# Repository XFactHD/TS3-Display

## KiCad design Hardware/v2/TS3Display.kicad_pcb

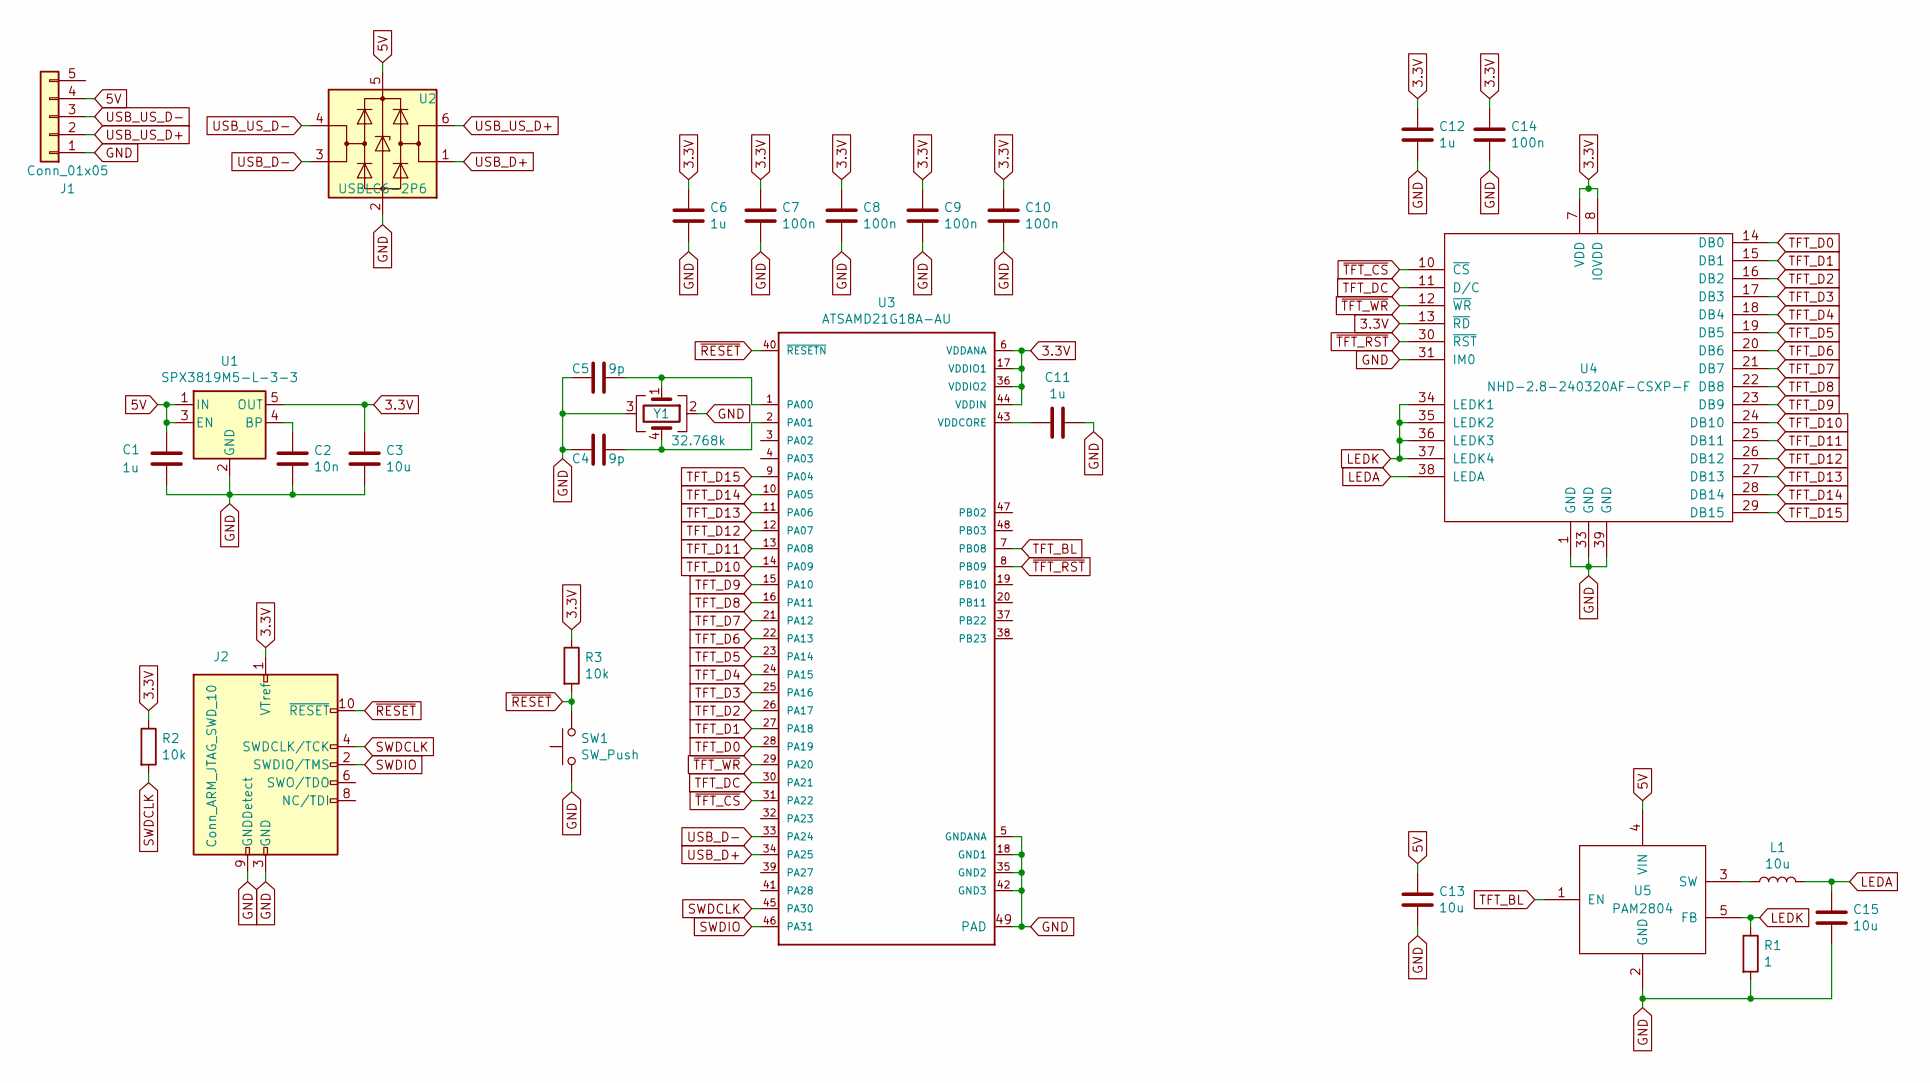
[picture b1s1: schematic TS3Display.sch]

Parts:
C1, C6, C11, C12: 1u; C_0805
C2: 10n; C_0805
C3, C13, C15: 10u; C_0805
C4, C5: 9p; C_0805
C7: 100n; C_0603
C8, C9, C10, C14: 100n; C_0805
J1: Conn_01x05; JST_SH_BM05B-SRSS-TB_05x1.00mm_Straight
J2: Conn_ARM_JTAG_SWD_10; Pin_Header_Straight_2x05_Pitch1.27mm_SMD
L1: 10u; L_Taiyo-Yuden_NR-40xx
R1: 1; R_0805
R2, R3: 10k; R_0805
SW1: SW_Push; SW_SPST_PTS810
U1: SPX3819M5-L-3-3; SOT-23-5
U2: USBLC6-2P6; SOT-23-6
U3: ATSAMD21G18A-AU; QFN-48-1EP_7x7mm_Pitch0.5mm
U4: NHD-2.8-240320AF-CSXP-F
U5: PAM2804; TSOT-23-5
Y1: 32.768k; Crystal_SMD_SeikoEpson_MC146-4pin_6.7x1.5mm

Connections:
3.3V: C3.1, C6.1, C7.1, C8.1, C9.1, C10.1, C12.1, C14.1, J2.1 (VTref), R2.1, R3.1, U1.5 (OUT), U3.6 (VDDANA), U3.17 (VDDIO1), U3.36 (VDDIO2), U3.44 (VDDIN), U4.7 (VDD), U4.8 (IOVDD), U4.13 (~RD)
5V: C1.1, C13.2, J1.4, U1.1 (IN), U1.3 (EN), U2.5 (VBUS), U5.4 (VIN)
GND: C1.2, C2.1, C3.2, C4.2, C5.2, C6.2, C7.2, C8.2, C9.2, C10.2, C11.1, C12.2, C13.1, C14.2, C15.1, J1.1, J2.3 (GND), J2.5 (GND), J2.9 (GNDDetect), R1.2, SW1.1, U1.2 (GND), U2.2 (GND), U3.5 (GNDANA), U3.18 (GND1), U3.35 (GND2), U3.42 (GND3), U3.49 (PAD), U4.1 (GND), U4.31 (IM0), U4.33 (GND), U4.39 (GND), U5.2 (GND), Y1.2, Y1.3
LEDA: C15.2, L1.2, U4.38 (LEDA)
LEDK: R1.1, U4.34 (LEDK1), U4.35 (LEDK2), U4.36 (LEDK3), U4.37 (LEDK4), U5.5 (FB)
unnamed: C2.2, U1.4 (BP)
unnamed: C4.1, U3.2 (PA01), Y1.4
unnamed: C5.1, U3.1 (PA00), Y1.1
unnamed: C11.2, U3.43 (VDDCORE)
unnamed: L1.1, U5.3 (SW)
SWDCLK: J2.4 (SWDCLK/TCK), R2.2, U3.45 (PA30)
SWDIO: J2.2 (SWDIO/TMS), U3.46 (PA31)
TFT_BL: U3.7 (PB08), U5.1 (EN)
TFT_D0: U3.28 (PA19), U4.14 (DB0)
TFT_D1: U3.27 (PA18), U4.15 (DB1)
TFT_D2: U3.26 (PA17), U4.16 (DB2)
TFT_D3: U3.25 (PA16), U4.17 (DB3)
TFT_D4: U3.24 (PA15), U4.18 (DB4)
TFT_D5: U3.23 (PA14), U4.19 (DB5)
TFT_D6: U3.22 (PA13), U4.20 (DB6)
TFT_D7: U3.21 (PA12), U4.21 (DB7)
TFT_D8: U3.16 (PA11), U4.22 (DB8)
TFT_D9: U3.15 (PA10), U4.23 (DB9)
TFT_D10: U3.14 (PA09), U4.24 (DB10)
TFT_D11: U3.13 (PA08), U4.25 (DB11)
TFT_D12: U3.12 (PA07), U4.26 (DB12)
TFT_D13: U3.11 (PA06), U4.27 (DB13)
TFT_D14: U3.10 (PA05), U4.28 (DB14)
TFT_D15: U3.9 (PA04), U4.29 (DB15)
TFT_DC: U3.30 (PA21), U4.11 (D/C)
USB_D+: U2.1 (I/O1), U3.34 (PA25)
USB_D-: U2.3 (I/O2), U3.33 (PA24)
USB_US_D+: J1.2, U2.6 (I/O1)
USB_US_D-: J1.3, U2.4 (I/O2)
~RESET: J2.10 (~RESET~), R3.2, SW1.2, U3.40 (~RESETN~)
~TFT_CS: U3.31 (PA22), U4.10 (~CS)
~TFT_RST: U3.8 (PB09), U4.30 (~RST)
~TFT_WR: U3.29 (PA20), U4.12 (~WR)

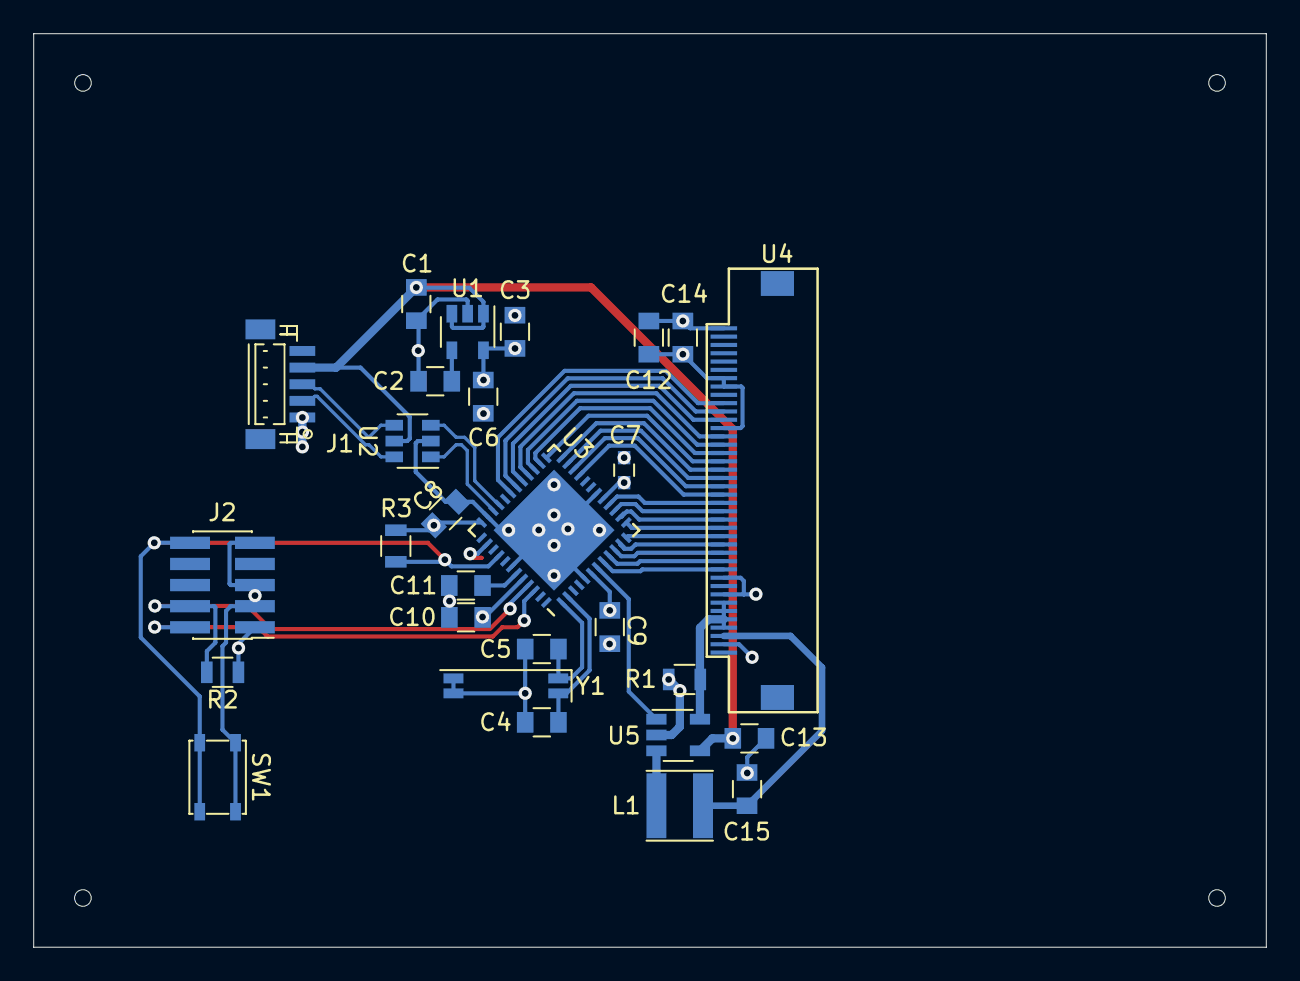
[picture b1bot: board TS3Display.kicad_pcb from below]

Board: 4 copper layers, 74.1 x 54.9 mm, 28 parts (27 on the bottom side), 38 nets.

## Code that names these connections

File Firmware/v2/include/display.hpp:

#ifndef DISPLAY_HPP
#define DISPLAY_HPP

#include <Arduino.h>
#include <SPI.h>
#include <Adafruit_I2CDevice.h>
#include "ST7789_16bit.hpp"

#include "client.hpp"
#include "icons.hpp"

#define PCB_V1

#ifdef __IMXRT1062__
#define TFT_RST 0
#define TFT_RD  17
#define TFT_WR  18
#define TFT_CS  20
#define TFT_DC  19
#define TFT_BL  255
#elif defined(PCB_V1)
#define TFT_RST 31 //PB23
#define TFT_RD  255
#define TFT_WR  18 //PA05
#define TFT_CS  15 //PB08
#define TFT_DC  16 //PB09
#define TFT_BL  30 //PB22
#else
#define TFT_RST 15 //PB08
#define TFT_RD  255
#define TFT_WR  11 //PA20
#define TFT_CS  20 //PA22
#define TFT_DC  12 //PA21
#define TFT_BL  15 //PB08
#endif

class client_t;

void initDisplay();
bool switchDarkMode(bool dark);
void setDisplayBrightness(uint8_t percent);
void configureColors();
void drawBackground();
void displayOn();
void displayOff();

void printServerName(char* name);
void printChannelName(char* name);
void redrawUserList(client_t** clients, uint16_t ownClientId);
int redrawUserListPartial(client_t** clients, int idx, uint16_t ownClientId);

void printUserName(uint8_t line, client_t* client, bool isMe);
void drawUserState(int line, uint8_t state);
void clearClientList();

#endif //DISPLAY_HPP

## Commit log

2020-12-18 Initial commit with Hardware and Firmware
2020-12-18 Add Plugin source
2020-12-18 Fix plugin project files, add license
2020-12-18 Move display library to proper place
2021-02-12 Implement better handling of multi byte chars
2021-02-15 Fix string copy crash in name sanitizer, cleanup logging, implement connection timeout
2021-02-15 Clear screen on command timeout
2021-03-05 Cleanup Firmware and Plugin code
2021-03-05 Use different connector for USB connection
2021-04-12 Fix crystal connections
2021-08-02 Fix mirrored LCD FPC pinout
2021-09-11 Restructure plugin project directories
2021-09-24 Adapt to Cortex M0 hardware, move headers to include dir, update to latest display code
2021-09-24 Add missing IM0 pin to display and tie to ground, fixes display not initializing
2021-09-25 Fix bitmap drawing not respecting display rotation
2021-09-25 Implement dark mode and brightness configs in display firmware
